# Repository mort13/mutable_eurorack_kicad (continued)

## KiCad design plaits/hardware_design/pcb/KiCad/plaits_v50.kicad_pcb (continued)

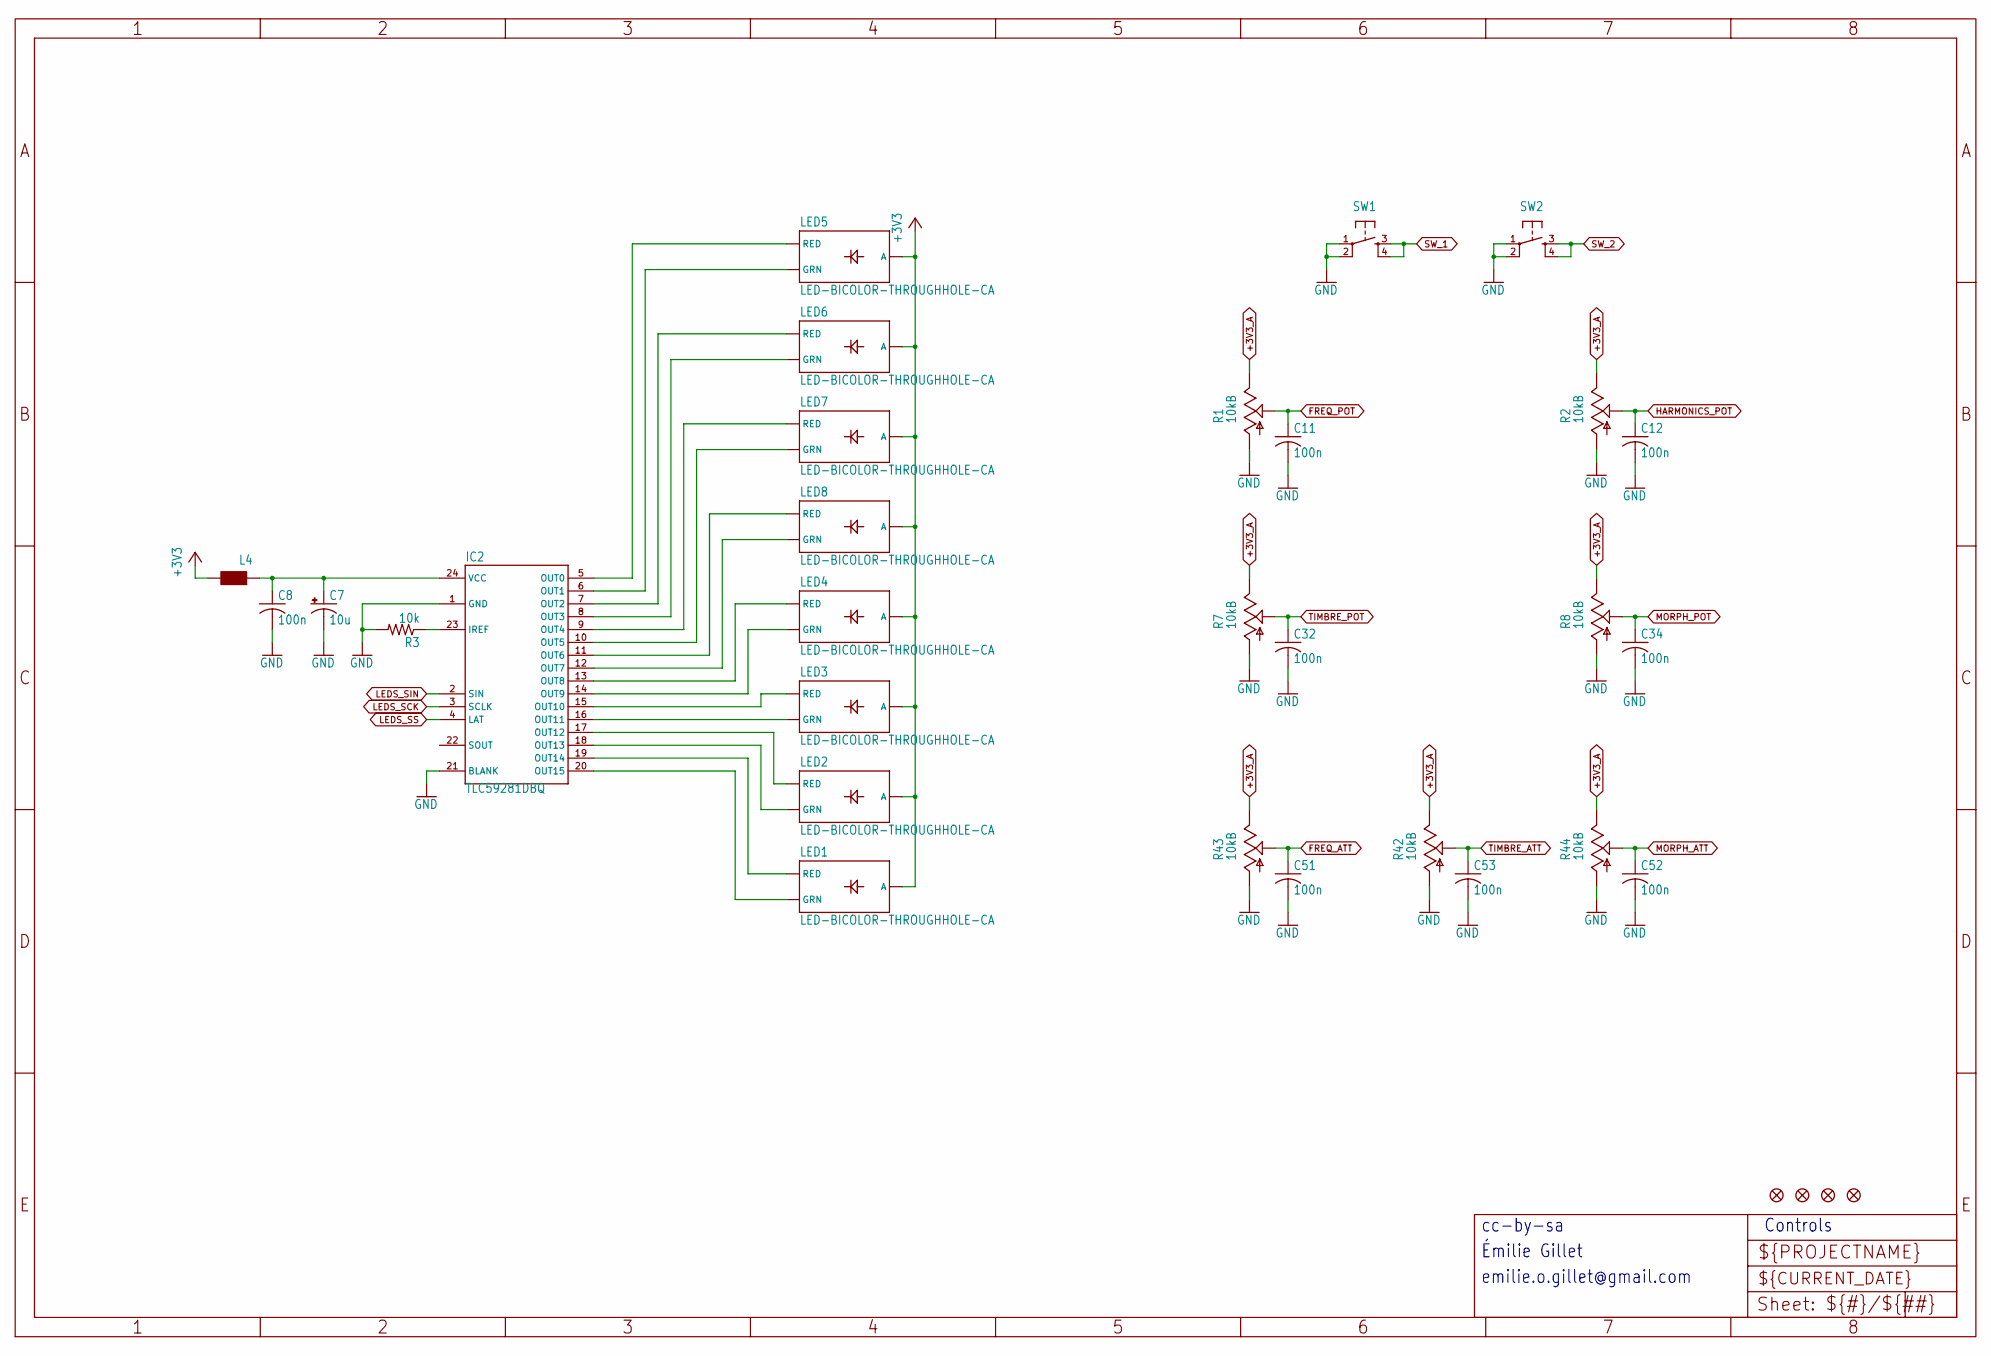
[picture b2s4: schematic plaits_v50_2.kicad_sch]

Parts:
C7: 10u; PANASONIC_A
C8, C11, C12, C32, C34, C51, C52, C53: 100n; C0402
IC2: TLC59281DBQ; TSSOP24_0635
JP1, JP2, JP3, JP4: FIDUCIAL1X2; FIDUCIAL-1X2
L4: WE-CBF_0603; 0603
LED1, LED2, LED3, LED4, LED5, LED6, LED7, LED8: LED-BICOLOR-THROUGHHOLE-CA; LED-BICOLOR-THROUGHHOLE-LUMEX
R1, R2, R7, R8: 10kB; ALPS_POT_VERTICAL_PS
R3: 10k; R0402
R42, R43, R44: 10kB; ALPS_POT_VERTICAL
SW1, SW2: TAC_SWITCHPTH; TACTILE-PTH

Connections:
+3V3: L4.2, LED1.A, LED2.A, LED3.A, LED4.A, LED5.A, LED6.A, LED7.A, LED8.A; also elsewhere on the board
+3V3_A: R1.P$1 (E), R2.P$1 (E), R7.P$1 (E), R8.P$1 (E), R42.P$1 (E), R43.P$1 (E), R44.P$1 (E); also elsewhere on the board
FREQ_ATT: C51.1, R43.P$2 (S); also elsewhere on the board
FREQ_POT: C11.1, R1.P$2 (S); also elsewhere on the board
GND: C7.-, C8.2, C11.2, C12.2, C32.2, C34.2, C51.2, C52.2, C53.2, IC2.1 (GND), IC2.21 (BLANK), R1.P$3 (A), R2.P$3 (A), R3.2, R7.P$3 (A), R8.P$3 (A), R42.P$3 (A), R43.P$3 (A), R44.P$3 (A), SW1.1, SW1.2, SW2.1, SW2.2; also elsewhere on the board
HARMONICS_POT: C12.1, R2.P$2 (S); also elsewhere on the board
LEDS_SCK: IC2.3 (SCLK); also elsewhere on the board
LEDS_SIN: IC2.2 (SIN); also elsewhere on the board
LEDS_SS: IC2.4 (LAT); also elsewhere on the board
MORPH_ATT: C52.1, R44.P$2 (S); also elsewhere on the board
MORPH_POT: C34.1, R8.P$2 (S); also elsewhere on the board
unnamed: IC2.12 (OUT7), LED8.GREEN_C (GRN)
unnamed: IC2.11 (OUT6), LED8.RED_C (RED)
unnamed: IC2.10 (OUT5), LED7.GREEN_C (GRN)
unnamed: IC2.9 (OUT4), LED7.RED_C (RED)
unnamed: IC2.8 (OUT3), LED6.GREEN_C (GRN)
unnamed: IC2.13 (OUT8), LED4.RED_C (RED)
unnamed: IC2.7 (OUT2), LED6.RED_C (RED)
unnamed: IC2.14 (OUT9), LED4.GREEN_C (GRN)
unnamed: IC2.6 (OUT1), LED5.GREEN_C (GRN)
unnamed: IC2.15 (OUT10), LED3.RED_C (RED)
unnamed: IC2.16 (OUT11), LED3.GREEN_C (GRN)
unnamed: IC2.17 (OUT12), LED2.RED_C (RED)
unnamed: IC2.18 (OUT13), LED2.GREEN_C (GRN)
unnamed: IC2.19 (OUT14), LED1.RED_C (RED)
unnamed: IC2.5 (OUT0), LED5.RED_C (RED)
unnamed: IC2.20 (OUT15), LED1.GREEN_C (GRN)
unnamed: C7.+, C8.1, IC2.24 (VCC), L4.1
unnamed: IC2.23 (IREF), R3.1
SW_1: SW1.3, SW1.4; also elsewhere on the board
SW_2: SW2.3, SW2.4; also elsewhere on the board
TIMBRE_ATT: C53.1, R42.P$2 (S); also elsewhere on the board
TIMBRE_POT: C32.1, R7.P$2 (S); also elsewhere on the board

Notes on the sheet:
emilie.o.gillet@gmail.com
Émilie Gillet
cc-by-sa
Controls

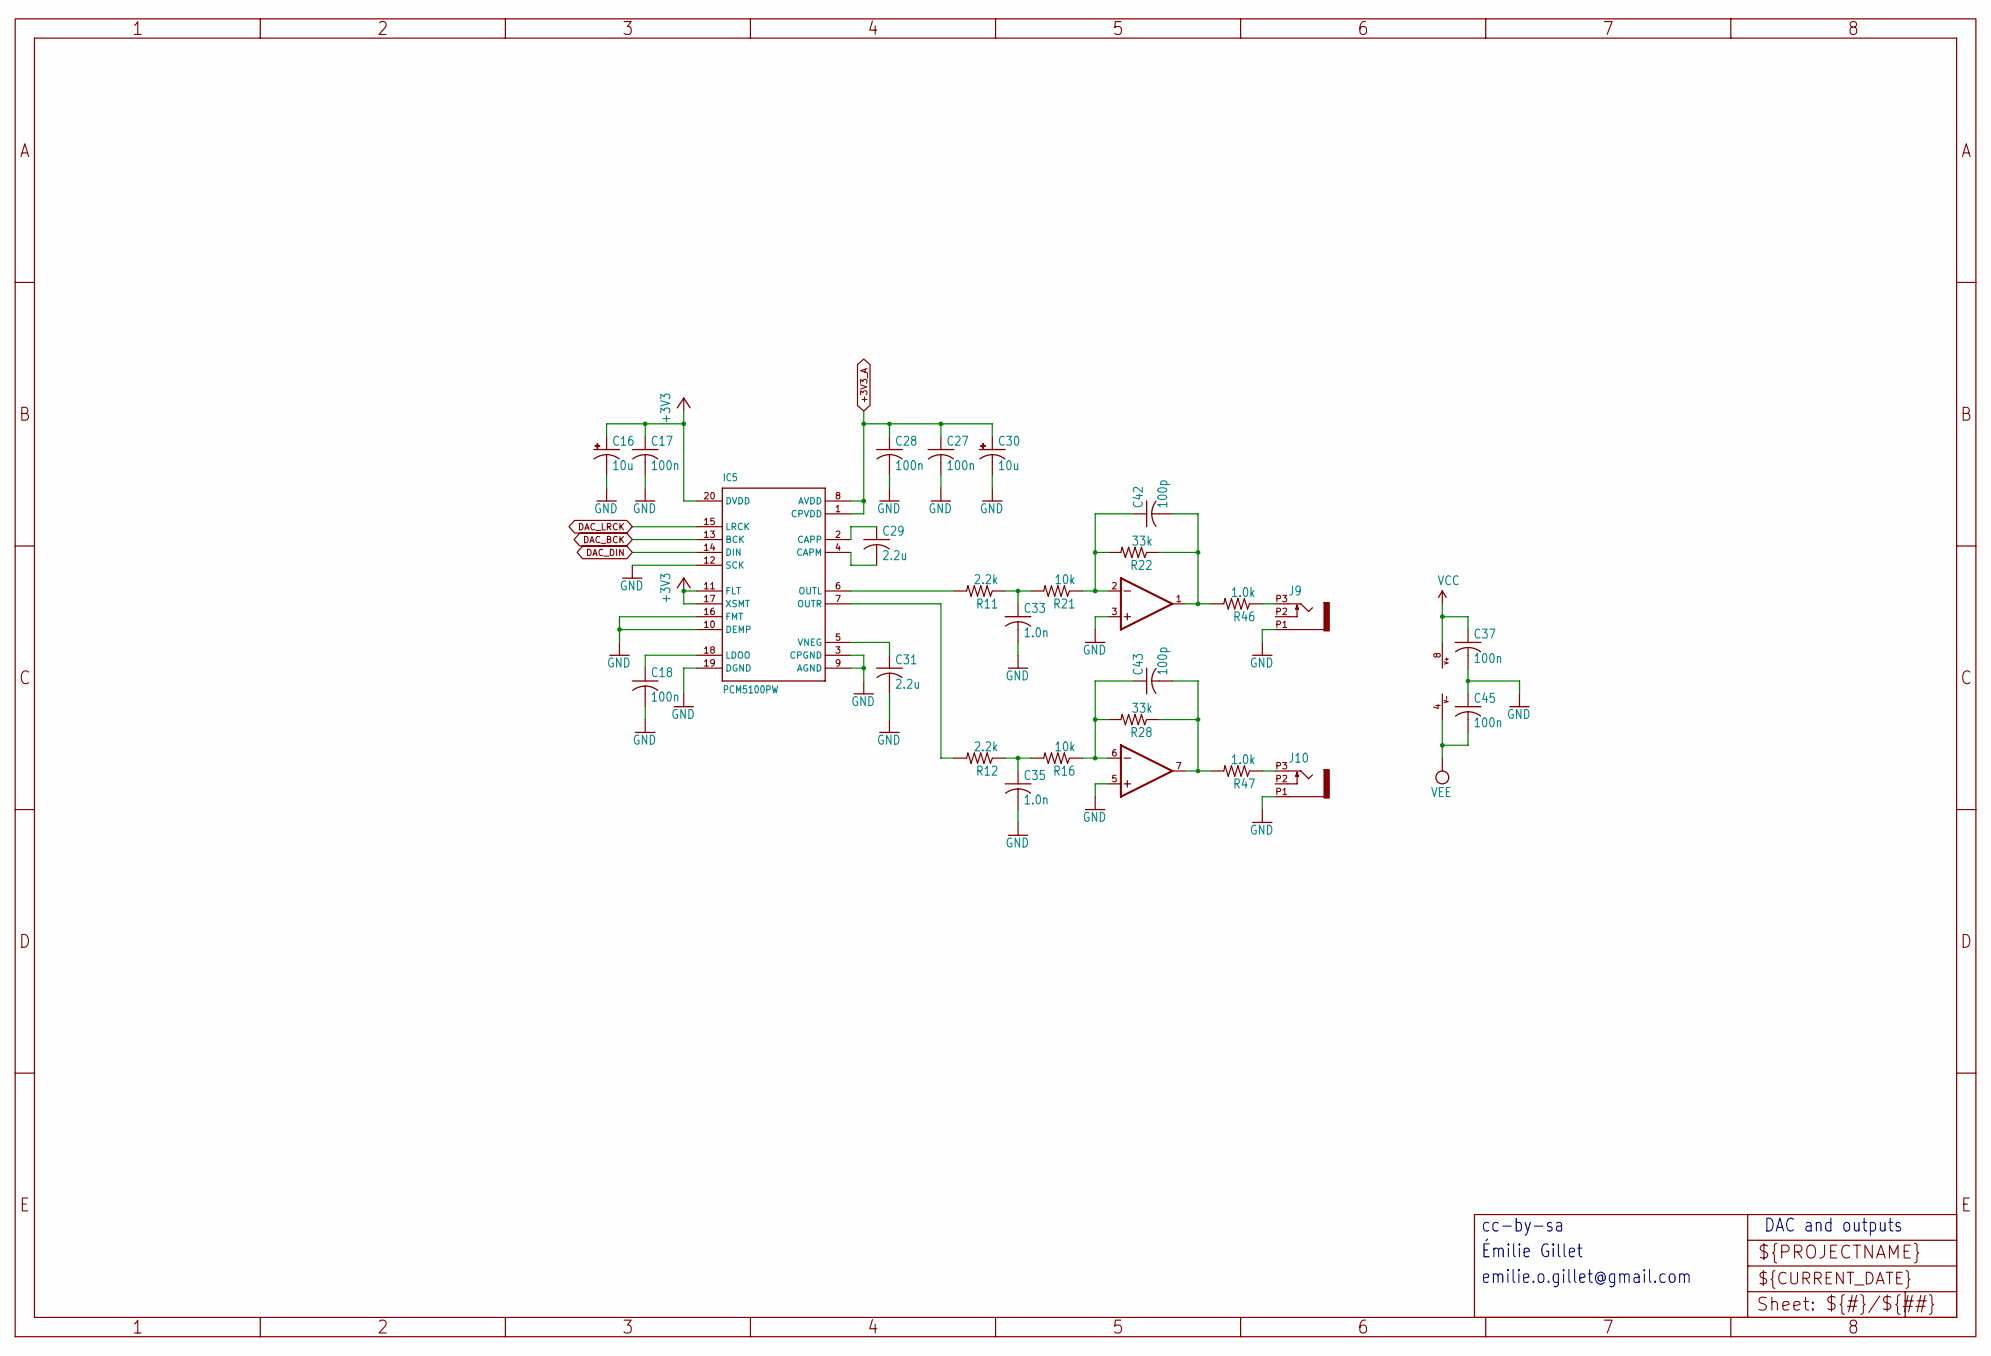
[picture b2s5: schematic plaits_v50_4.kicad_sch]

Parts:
C16, C30: 10u; PANASONIC_A
C17, C18, C27, C28, C37, C45: 100n; C0402
C29, C31: 2.2u; C0805
C33, C35: 1.0n; C0402
C42, C43: 100p; C0402
IC5: PCM5100PW; SSOP20
IC8: TL072PW; TSSOP08
J9, J10: PJ301_THONKICONN6; WQP_PJ_301M6
R11, R12: 2.2k; R0402
R16, R21: 10k; R0402
R22, R28: 33k; R0402
R46, R47: 1.0k; R0603

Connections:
+3V3: C16.+, C17.1, IC5.11 (FLT), IC5.17 (XSMT), IC5.20 (DVDD); also elsewhere on the board
+3V3_A: C27.1, C28.1, C30.+, IC5.1 (CPVDD), IC5.8 (AVDD); also elsewhere on the board
DAC_BCK: IC5.13 (BCK); also elsewhere on the board
DAC_DIN: IC5.14 (DIN); also elsewhere on the board
DAC_LRCK: IC5.15 (LRCK); also elsewhere on the board
GND: C16.-, C17.2, C18.2, C27.2, C28.2, C30.-, C31.2, C33.2, C35.2, C37.2, C45.1, IC5.3 (CPGND), IC5.9 (AGND), IC5.10 (DEMP), IC5.12 (SCK), IC5.16 (FMT), IC5.19 (DGND), IC8.3 (+IN), IC8.5 (+IN), J9.P1 (1), J10.P1 (1); also elsewhere on the board
unnamed: C29.1, IC5.2 (CAPP)
unnamed: C29.2, IC5.4 (CAPM)
unnamed: IC5.6 (OUTL), R11.2
unnamed: C33.1, R11.1, R21.2
unnamed: C35.1, R12.1, R16.2
unnamed: C31.1, IC5.5 (VNEG)
unnamed: C18.1, IC5.18 (LDOO)
unnamed: IC5.7 (OUTR), R12.2
unnamed: C43.1, IC8.6 (-IN), R16.1, R28.2
unnamed: C43.2, IC8.7 (OUT), R28.1, R47.2
unnamed: C42.1, IC8.2 (-IN), R21.1, R22.2
unnamed: C42.2, IC8.1 (OUT), R22.1, R46.2
unnamed: J9.P3 (3), R46.1
unnamed: J10.P3 (3), R47.1
VCC: C37.1, IC8.8 (V+); also elsewhere on the board
VEE: C45.2, IC8.4 (V-); also elsewhere on the board

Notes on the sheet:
emilie.o.gillet@gmail.com
Émilie Gillet
DAC and outputs
cc-by-sa

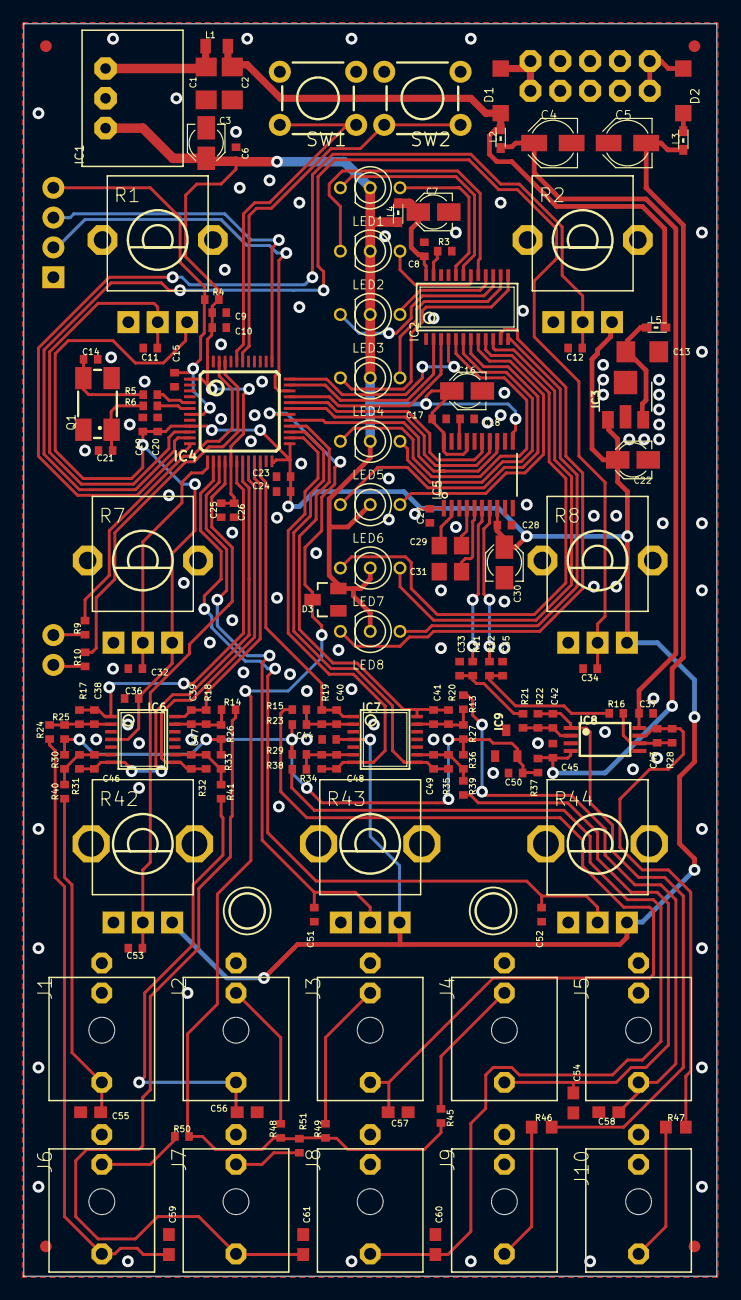
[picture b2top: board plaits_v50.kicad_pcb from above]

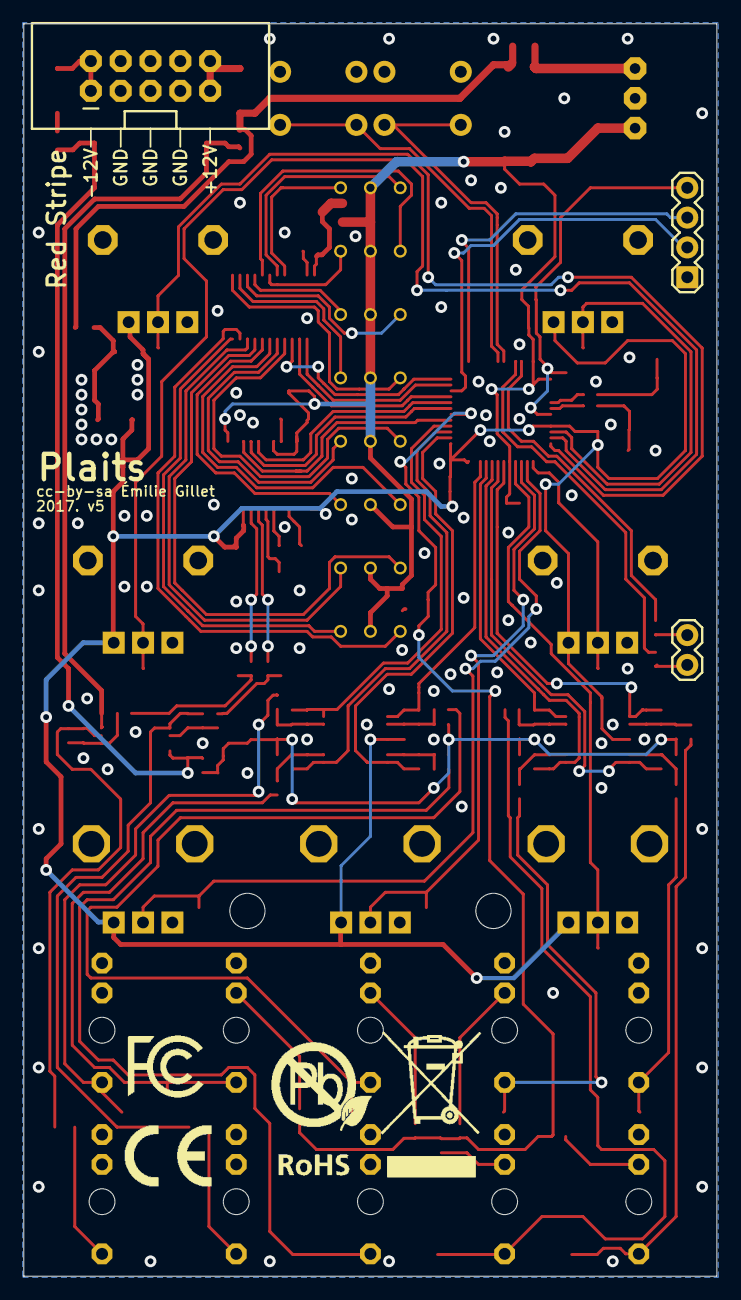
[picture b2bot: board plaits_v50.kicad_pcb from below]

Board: 2 copper layers, 59.0 x 106.7 mm, 162 parts (6 on the bottom side), 100 nets.

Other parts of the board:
U$1: FCC_MEDIUM
U$2: ROHS_BIG
U$3: CE_MEDIUM

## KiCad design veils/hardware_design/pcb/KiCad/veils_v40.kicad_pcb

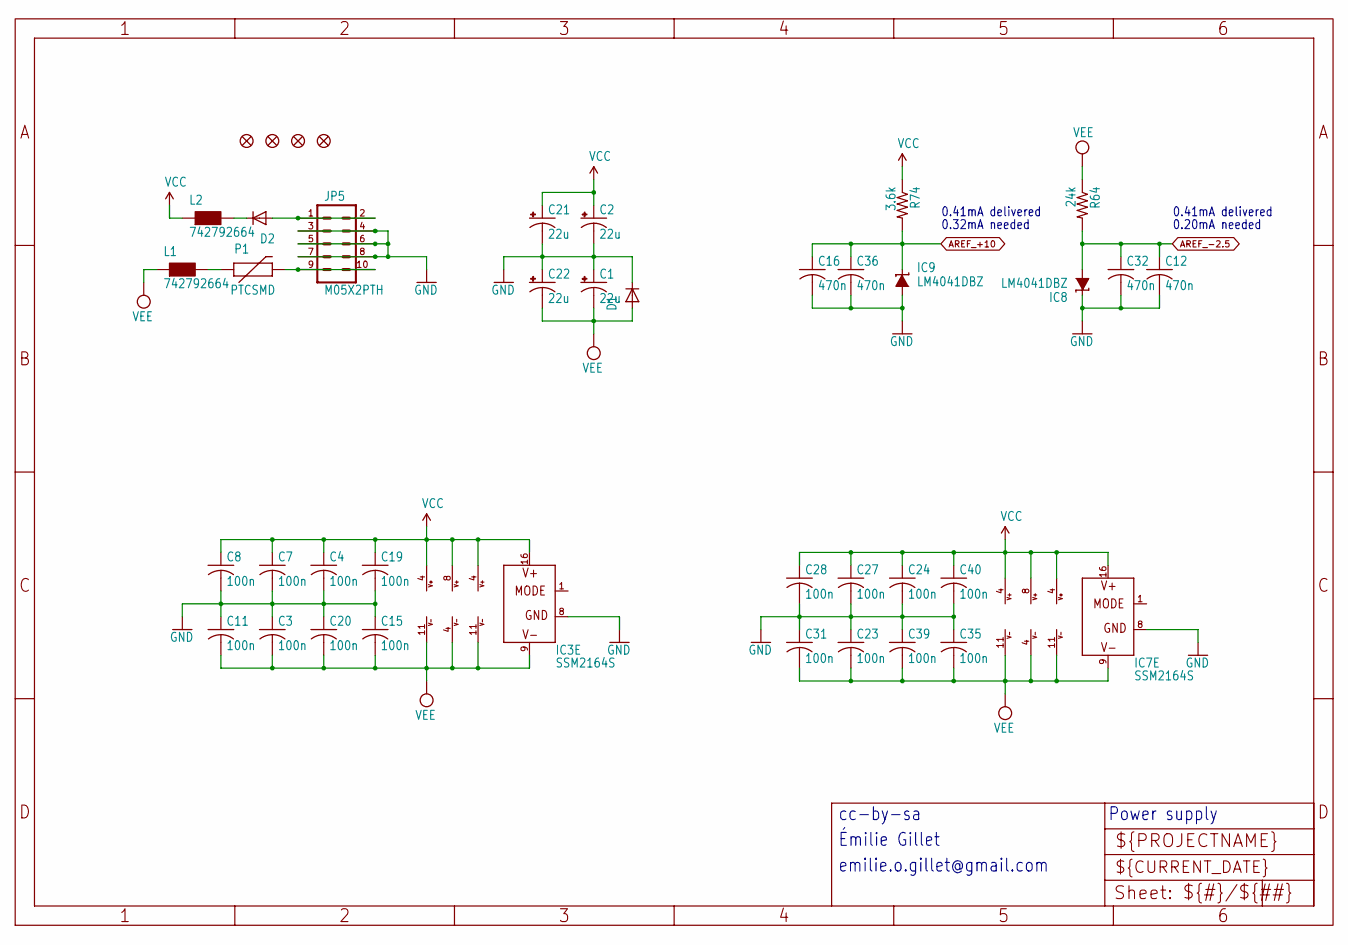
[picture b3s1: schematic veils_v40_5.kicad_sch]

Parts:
C1, C2, C21, C22: 22u; PANASONIC_B
C3, C4, C7, C8, C11, C15, C19, C20, C23, C24, C27, C28, C31, C35, C39, C40: 100n; C0402
C12, C16, C32, C36: 470n; C0402
D1, D2: 1N5819HW; SOD123
IC1, IC4, IC5, IC10: TL074PW; TSSOP14
IC2, IC6: TL072PW; TSSOP8
IC3, IC7: SSM2164S; SOIC16N
IC8, IC9: LM4041DBZ; DBZ_R-PDSO-G3
JP1, JP2, JP3, JP4: FIDUCIAL1X2; FIDUCIAL-1X2
JP5: M05X2PTH; AVR_ICSP
L1, L2: 742792664; 0603
P1: PTCSMD; PTC-1206
R64: 24k; R0402
R74: 3.6k; R0402

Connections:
AREF_+10: C16.1, C36.1, IC9.1 (C), R74.2; also elsewhere on the board
AREF_-2.5: C12.1, C32.1, IC8.2 (A), R64.2; also elsewhere on the board
GND: C1.+, C2.-, C3.1, C4.2, C7.2, C8.2, C11.1, C12.2, C15.1, C16.2, C19.2, C20.1, C21.-, C22.+, C23.1, C24.2, C27.2, C28.2, C31.1, C32.2, C35.1, C36.2, C39.1, C40.2, D1.C, IC3.8 (GND), IC7.8 (GND), IC8.1 (C), IC9.2 (A), JP5.3, JP5.4, JP5.5, JP5.6, JP5.7, JP5.8; also elsewhere on the board
unnamed: D2.A, JP5.1, JP5.2
unnamed: JP5.9, JP5.10, P1.2
unnamed: L1.2, P1.1
unnamed: D2.C, L2.2
VCC: C2.+, C4.1, C7.1, C8.1, C19.1, C21.+, C24.1, C27.1, C28.1, C40.1, IC1.4 (V+), IC2.8 (V+), IC3.16 (V+), IC4.4 (V+), IC5.4 (V+), IC6.8 (V+), IC7.16 (V+), IC10.4 (V+), L2.1, R74.1
VEE: C1.-, C3.2, C11.2, C15.2, C20.2, C22.-, C23.2, C31.2, C35.2, C39.2, D1.A, IC1.11 (V-), IC2.4 (V-), IC3.9 (V-), IC4.11 (V-), IC5.11 (V-), IC6.4 (V-), IC7.9 (V-), IC10.11 (V-), L1.1, R64.1

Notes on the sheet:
Power supply
0.41mA delivered
Émilie Gillet
0.32mA needed
0.20mA needed
cc-by-sa
emilie.o.gillet@gmail.com

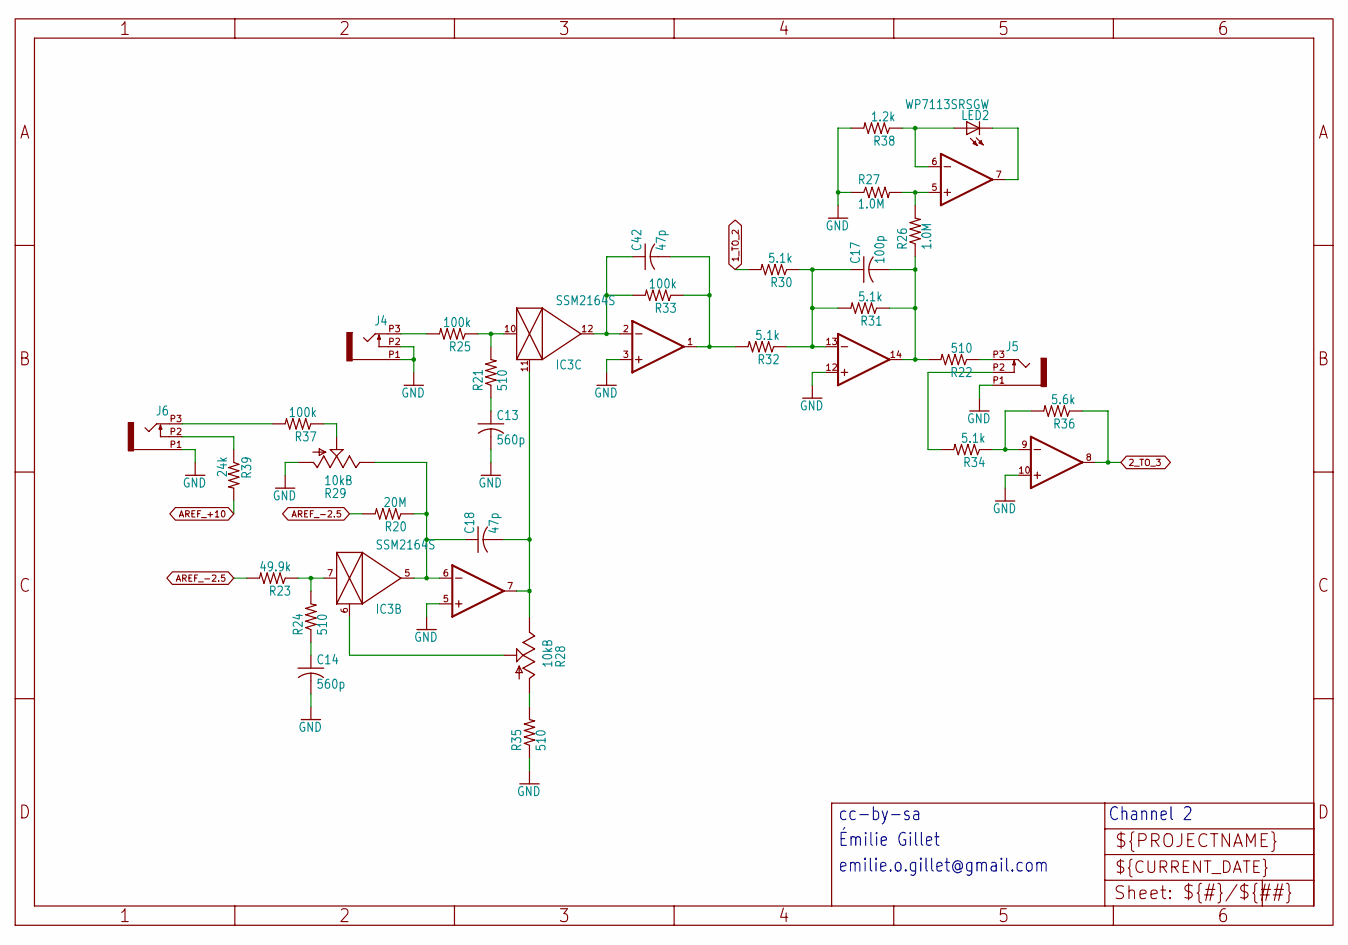
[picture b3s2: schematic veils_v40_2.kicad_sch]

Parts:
C13, C14: 560p; C0402
C17: 100p; C0402
C18, C42: 47p; C0402
IC2: TL072PW; TSSOP8
IC3: SSM2164S; SOIC16N
IC4: TL074PW; TSSOP14
J4, J5, J6: PJ301_THONKICONN6; WQP_PJ_301M6
LED2: WP7113SRSGW; LED5MM
R20: 20M; R0402
R21, R22, R24, R35: 510; R0402
R23: 49.9k; R0402
R25, R33, R37: 100k; R0402
R26, R27: 1.0M; R0402
R28: 10kB; ALPS_POT_VERTICAL
R29: 10kB; ALPS_POT_VERTICAL_PS
R30, R31, R32, R34: 5.1k; R0402
R36: 5.6k; R0402
R38: 1.2k; R0402
R39: 24k; R0402

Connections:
1_TO_2: R30.2; also elsewhere on the board
2_TO_3: IC4.8 (OUT), R36.1; also elsewhere on the board
AREF_+10: R39.2; also elsewhere on the board
AREF_-2.5: R20.2, R23.2; also elsewhere on the board
FOO1: IC3.7 (IN), R23.1, R24.2
GND: C13.2, C14.2, IC4.3 (+IN), IC4.5 (+IN), IC4.10 (+IN), IC4.12 (+IN), J4.P1 (1), J4.P2 (2), J5.P1 (1), J6.P1 (1), R27.1, R29.P$3 (A), R35.1, R38.2; also elsewhere on the board
unnamed: J4.P3 (3), R25.2
unnamed: IC2.5 (+IN), R26.2, R27.2
unnamed: J5.P3 (3), R22.1
unnamed: C13.1, R21.1
unnamed: IC3.10 (IN), R21.2, R25.1
unnamed: IC3.6 (CTRL), R28.P$2 (S)
unnamed: C17.1, IC4.13 (-IN), R30.1, R31.2, R32.1
unnamed: C18.2, IC3.11 (CTRL), IC4.7 (OUT), R28.P$1 (E)
unnamed: R28.P$3 (A), R35.2
unnamed: IC2.7 (OUT), LED2.K (C)
unnamed: IC2.6 (-IN), LED2.A, R38.1
unnamed: IC4.9 (-IN), R34.1, R36.2
unnamed: J5.P2 (2), R34.2
unnamed: C42.2, IC4.1 (OUT), R32.2, R33.1
unnamed: R29.P$2 (S), R37.1
unnamed: C14.1, R24.1
unnamed: C18.1, IC3.5 (OUT), IC4.6 (-IN), R20.1, R29.P$1 (E)
unnamed: J6.P3 (3), R37.2
unnamed: C42.1, IC3.12 (OUT), IC4.2 (-IN), R33.2
unnamed: J6.P2 (2), R39.1
OUT2: C17.2, IC4.14 (OUT), R22.2, R26.1, R31.1

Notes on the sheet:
Émilie Gillet
Channel 2
cc-by-sa
emilie.o.gillet@gmail.com

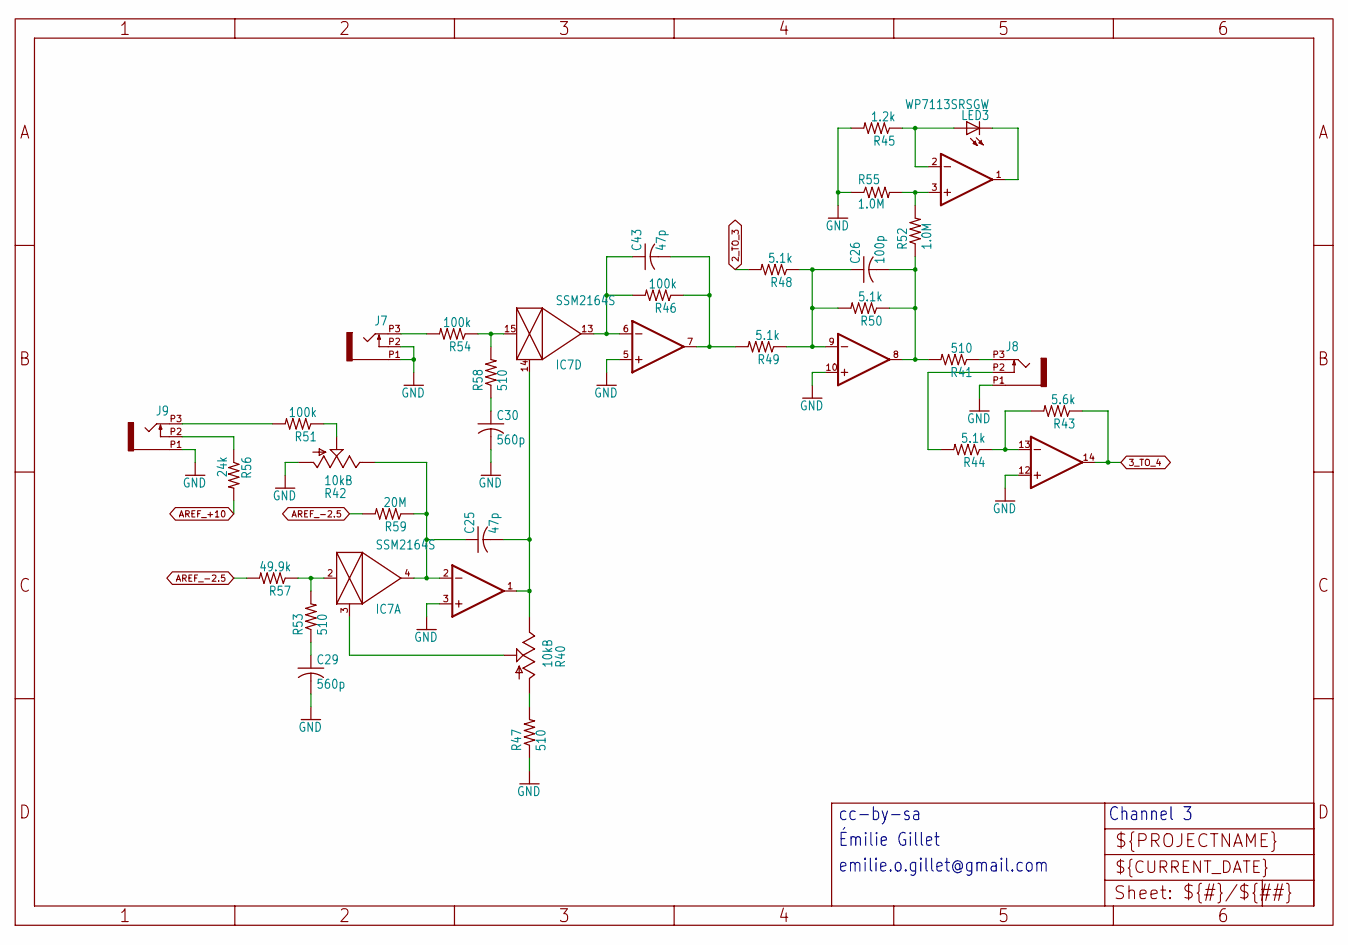
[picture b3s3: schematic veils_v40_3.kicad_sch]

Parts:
C25, C43: 47p; C0402
C26: 100p; C0402
C29, C30: 560p; C0402
IC5: TL074PW; TSSOP14
IC6: TL072PW; TSSOP8
IC7: SSM2164S; SOIC16N
J7, J8, J9: PJ301_THONKICONN6; WQP_PJ_301M6
LED3: WP7113SRSGW; LED5MM
R40: 10kB; ALPS_POT_VERTICAL
R41, R47, R53, R58: 510; R0402
R42: 10kB; ALPS_POT_VERTICAL_PS
R43: 5.6k; R0402
R44, R48, R49, R50: 5.1k; R0402
R45: 1.2k; R0402
R46, R51, R54: 100k; R0402
R52, R55: 1.0M; R0402
R56: 24k; R0402
R57: 49.9k; R0402
R59: 20M; R0402

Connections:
2_TO_3: R48.2; also elsewhere on the board
3_TO_4: IC5.14 (OUT), R43.1; also elsewhere on the board
AREF_+10: R56.2; also elsewhere on the board
AREF_-2.5: R57.2, R59.2; also elsewhere on the board
FOO2: IC7.2 (IN), R53.2, R57.1
GND: C29.2, C30.2, IC5.3 (+IN), IC5.5 (+IN), IC5.10 (+IN), IC5.12 (+IN), J7.P1 (1), J7.P2 (2), J8.P1 (1), J9.P1 (1), R42.P$3 (A), R45.2, R47.1, R55.1; also elsewhere on the board
unnamed: IC6.3 (+IN), R52.2, R55.2
unnamed: J8.P3 (3), R41.1
unnamed: IC7.3 (CTRL), R40.P$2 (S)
unnamed: C25.2, IC5.1 (OUT), IC7.14 (CTRL), R40.P$1 (E)
unnamed: R40.P$3 (A), R47.2
unnamed: C30.1, R58.1
unnamed: IC7.15 (IN), R54.1, R58.2
unnamed: C26.1, IC5.9 (-IN), R48.1, R49.1, R50.2
unnamed: J9.P2 (2), R56.1
unnamed: J7.P3 (3), R54.2
unnamed: J9.P3 (3), R51.2
unnamed: C43.1, IC5.6 (-IN), IC7.13 (OUT), R46.2
unnamed: IC6.1 (OUT), LED3.K (C)
unnamed: IC6.2 (-IN), LED3.A, R45.1
unnamed: IC5.13 (-IN), R43.2, R44.1
unnamed: J8.P2 (2), R44.2
unnamed: C29.1, R53.1
unnamed: C25.1, IC5.2 (-IN), IC7.4 (OUT), R42.P$1 (E), R59.1
unnamed: R42.P$2 (S), R51.1
unnamed: C43.2, IC5.7 (OUT), R46.1, R49.2
OUT3: C26.2, IC5.8 (OUT), R41.2, R50.1, R52.1

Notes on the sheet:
Émilie Gillet
Channel 3
cc-by-sa
emilie.o.gillet@gmail.com

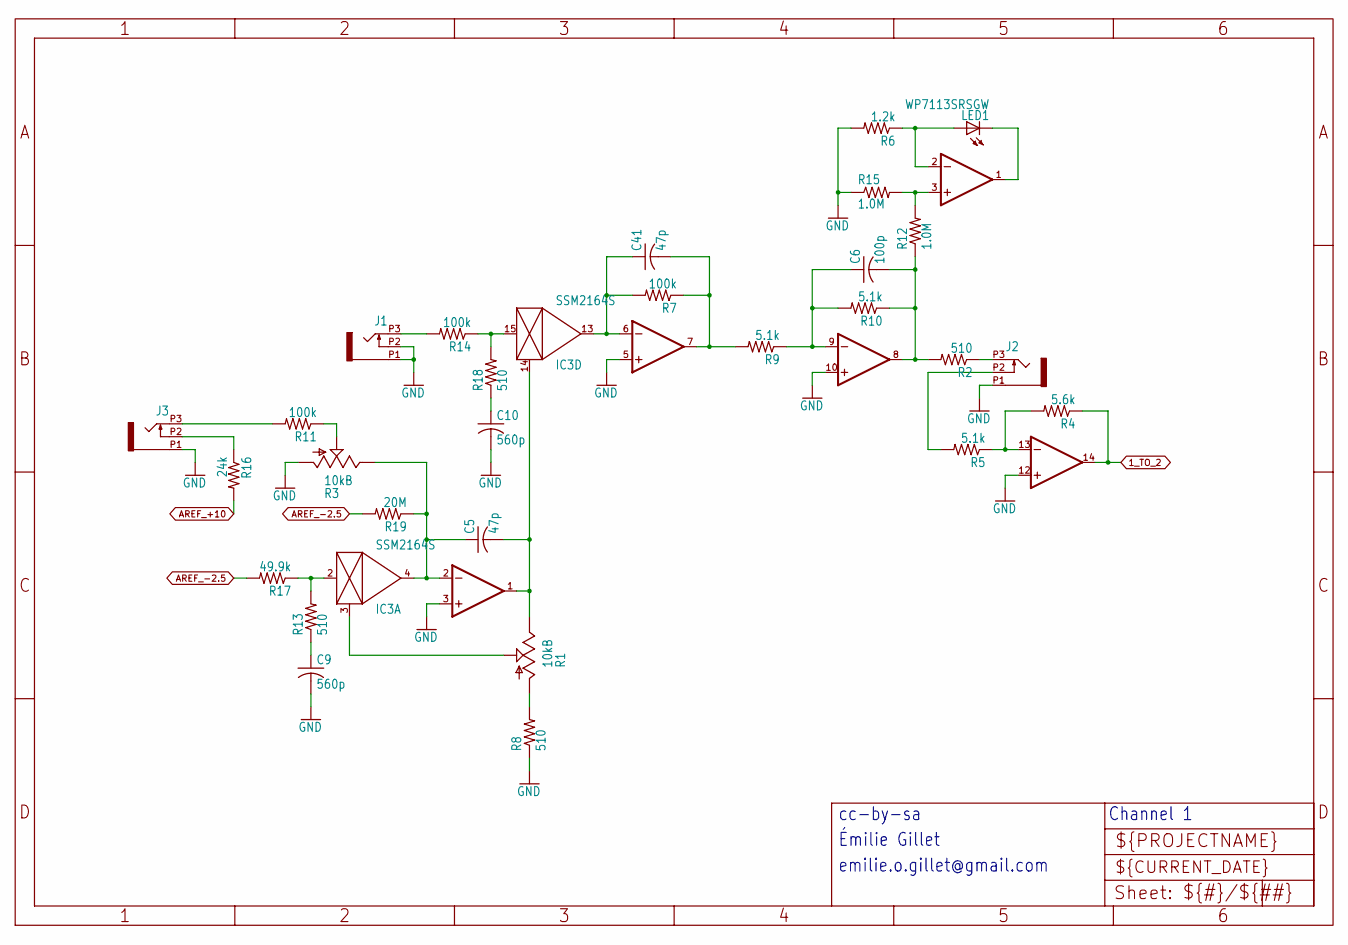
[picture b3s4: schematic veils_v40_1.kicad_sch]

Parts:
C5, C41: 47p; C0402
C6: 100p; C0402
C9, C10: 560p; C0402
IC1: TL074PW; TSSOP14
IC2: TL072PW; TSSOP8
IC3: SSM2164S; SOIC16N
J1, J2, J3: PJ301_THONKICONN6; WQP_PJ_301M6
LED1: WP7113SRSGW; LED5MM
R1: 10kB; ALPS_POT_VERTICAL
R2, R8, R13, R18: 510; R0402
R3: 10kB; ALPS_POT_VERTICAL_PS
R4: 5.6k; R0402
R5, R9, R10: 5.1k; R0402
R6: 1.2k; R0402
R7, R11, R14: 100k; R0402
R12, R15: 1.0M; R0402
R16: 24k; R0402
R17: 49.9k; R0402
R19: 20M; R0402

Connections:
1_TO_2: IC1.14 (OUT), R4.1; also elsewhere on the board
AREF_+10: R16.2; also elsewhere on the board
AREF_-2.5: R17.2, R19.2; also elsewhere on the board
CV_IN_1: J3.P3 (3), R11.2
FOO: IC3.2 (IN), R13.2, R17.1
GND: C9.2, C10.2, IC1.3 (+IN), IC1.5 (+IN), IC1.10 (+IN), IC1.12 (+IN), J1.P1 (1), J1.P2 (2), J2.P1 (1), J3.P1 (1), R3.P$3 (A), R6.2, R8.1, R15.1; also elsewhere on the board
unnamed: IC2.3 (+IN), R12.2, R15.2
unnamed: J2.P3 (3), R2.1
unnamed: IC3.3 (CTRL), R1.P$2 (S)
unnamed: C6.1, IC1.9 (-IN), R9.1, R10.2
unnamed: R3.P$2 (S), R11.1
unnamed: R1.P$3 (A), R8.2
unnamed: IC2.1 (OUT), LED1.K (C)
unnamed: IC2.2 (-IN), LED1.A, R6.1
unnamed: C9.1, R13.1
unnamed: J3.P2 (2), R16.1
unnamed: IC1.13 (-IN), R4.2, R5.1
unnamed: J2.P2 (2), R5.2
unnamed: C10.1, R18.1
unnamed: C5.1, IC1.2 (-IN), IC3.4 (OUT), R3.P$1 (E), R19.1
unnamed: J1.P3 (3), R14.2
unnamed: IC3.15 (IN), R14.1, R18.2
unnamed: C5.2, IC1.1 (OUT), IC3.14 (CTRL), R1.P$1 (E)
unnamed: C41.1, IC1.6 (-IN), IC3.13 (OUT), R7.2
unnamed: C41.2, IC1.7 (OUT), R7.1, R9.2
OUT1: C6.2, IC1.8 (OUT), R2.2, R10.1, R12.1

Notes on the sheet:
emilie.o.gillet@gmail.com
Channel 1
Émilie Gillet
cc-by-sa

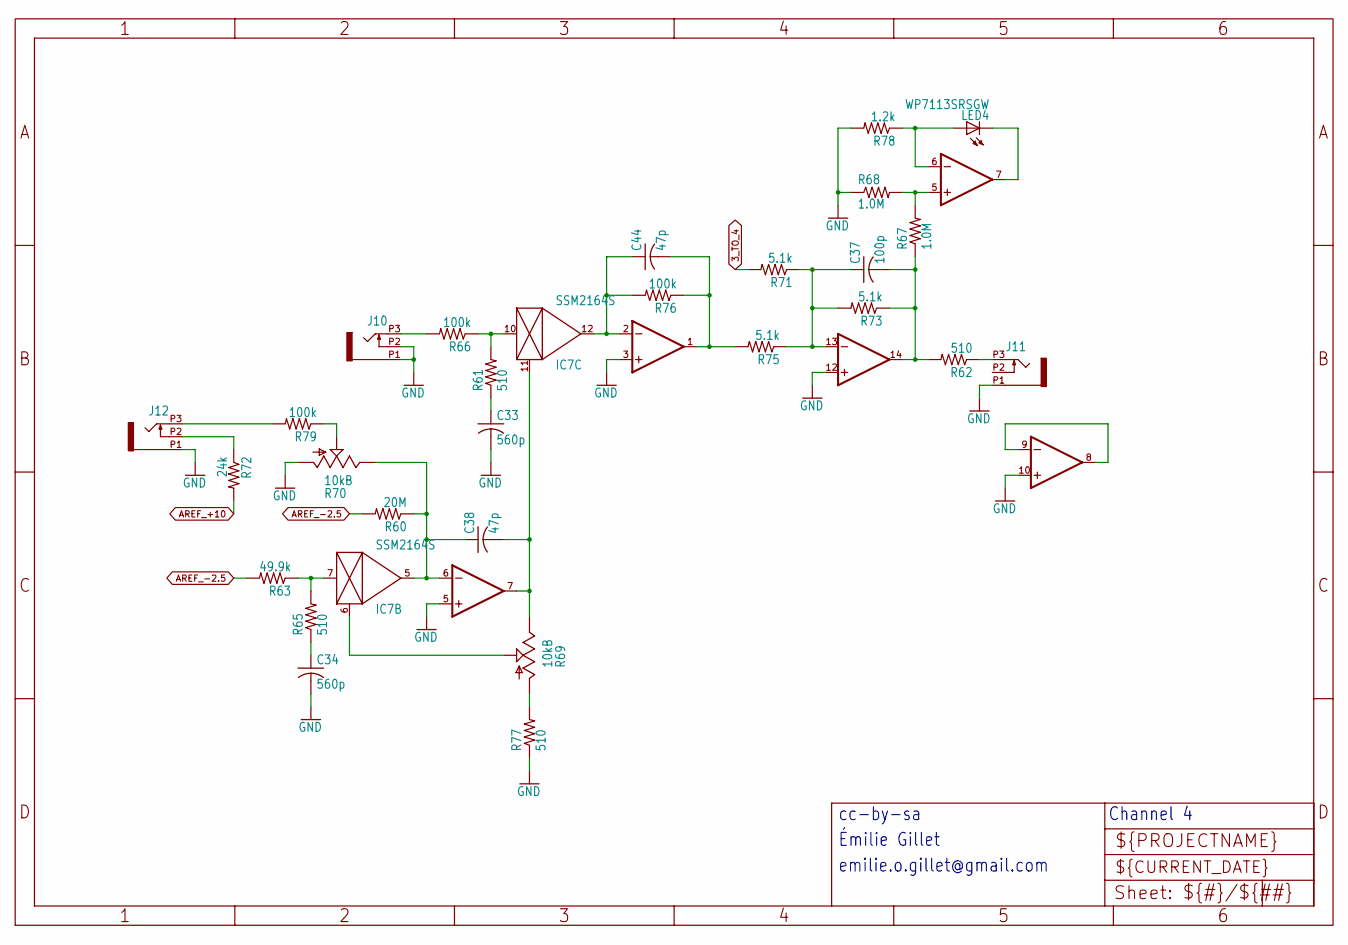
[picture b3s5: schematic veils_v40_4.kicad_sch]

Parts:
C33, C34: 560p; C0402
C37: 100p; C0402
C38, C44: 47p; C0402
IC6: TL072PW; TSSOP8
IC7: SSM2164S; SOIC16N
IC10: TL074PW; TSSOP14
J10, J11, J12: PJ301_THONKICONN6; WQP_PJ_301M6
LED4: WP7113SRSGW; LED5MM
R60: 20M; R0402
R61, R62, R65, R77: 510; R0402
R63: 49.9k; R0402
R66, R76, R79: 100k; R0402
R67, R68: 1.0M; R0402
R69: 10kB; ALPS_POT_VERTICAL
R70: 10kB; ALPS_POT_VERTICAL_PS
R71, R73, R75: 5.1k; R0402
R72: 24k; R0402
R78: 1.2k; R0402

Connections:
3_TO_4: R71.2; also elsewhere on the board
AREF_+10: R72.2; also elsewhere on the board
AREF_-2.5: R60.2, R63.2; also elsewhere on the board
FOO3: IC7.7 (IN), R63.1, R65.2
GND: C33.2, C34.2, IC10.3 (+IN), IC10.5 (+IN), IC10.10 (+IN), IC10.12 (+IN), J10.P1 (1), J10.P2 (2), J11.P1 (1), J12.P1 (1), R68.1, R70.P$3 (A), R77.1, R78.2; also elsewhere on the board
unnamed: IC10.8 (OUT), IC10.9 (-IN)
unnamed: IC6.5 (+IN), R67.2, R68.2
unnamed: C38.2, IC7.11 (CTRL), IC10.7 (OUT), R69.P$1 (E)
unnamed: IC7.6 (CTRL), R69.P$2 (S)
unnamed: R69.P$3 (A), R77.2
unnamed: C44.1, IC7.12 (OUT), IC10.2 (-IN), R76.2
unnamed: J10.P3 (3), R66.2
unnamed: J11.P3 (3), R62.1
unnamed: C33.1, R61.1
unnamed: IC7.10 (IN), R61.2, R66.1
unnamed: C37.1, IC10.13 (-IN), R71.1, R73.2, R75.1
unnamed: J12.P3 (3), R79.2
unnamed: IC6.7 (OUT), LED4.K (C)
unnamed: IC6.6 (-IN), LED4.A, R78.1
unnamed: C44.2, IC10.1 (OUT), R75.2, R76.1
unnamed: R70.P$2 (S), R79.1
unnamed: C34.1, R65.1
unnamed: C38.1, IC7.5 (OUT), IC10.6 (-IN), R60.1, R70.P$1 (E)
unnamed: J12.P2 (2), R72.1
OUT4: C37.2, IC10.14 (OUT), R62.2, R67.1, R73.1

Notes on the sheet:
cc-by-sa
emilie.o.gillet@gmail.com
Channel 4
Émilie Gillet
